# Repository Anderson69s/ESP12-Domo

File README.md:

# ESP12-Domo

More informations : https://atelierdumaker.com/portfolio/esp12-domo/

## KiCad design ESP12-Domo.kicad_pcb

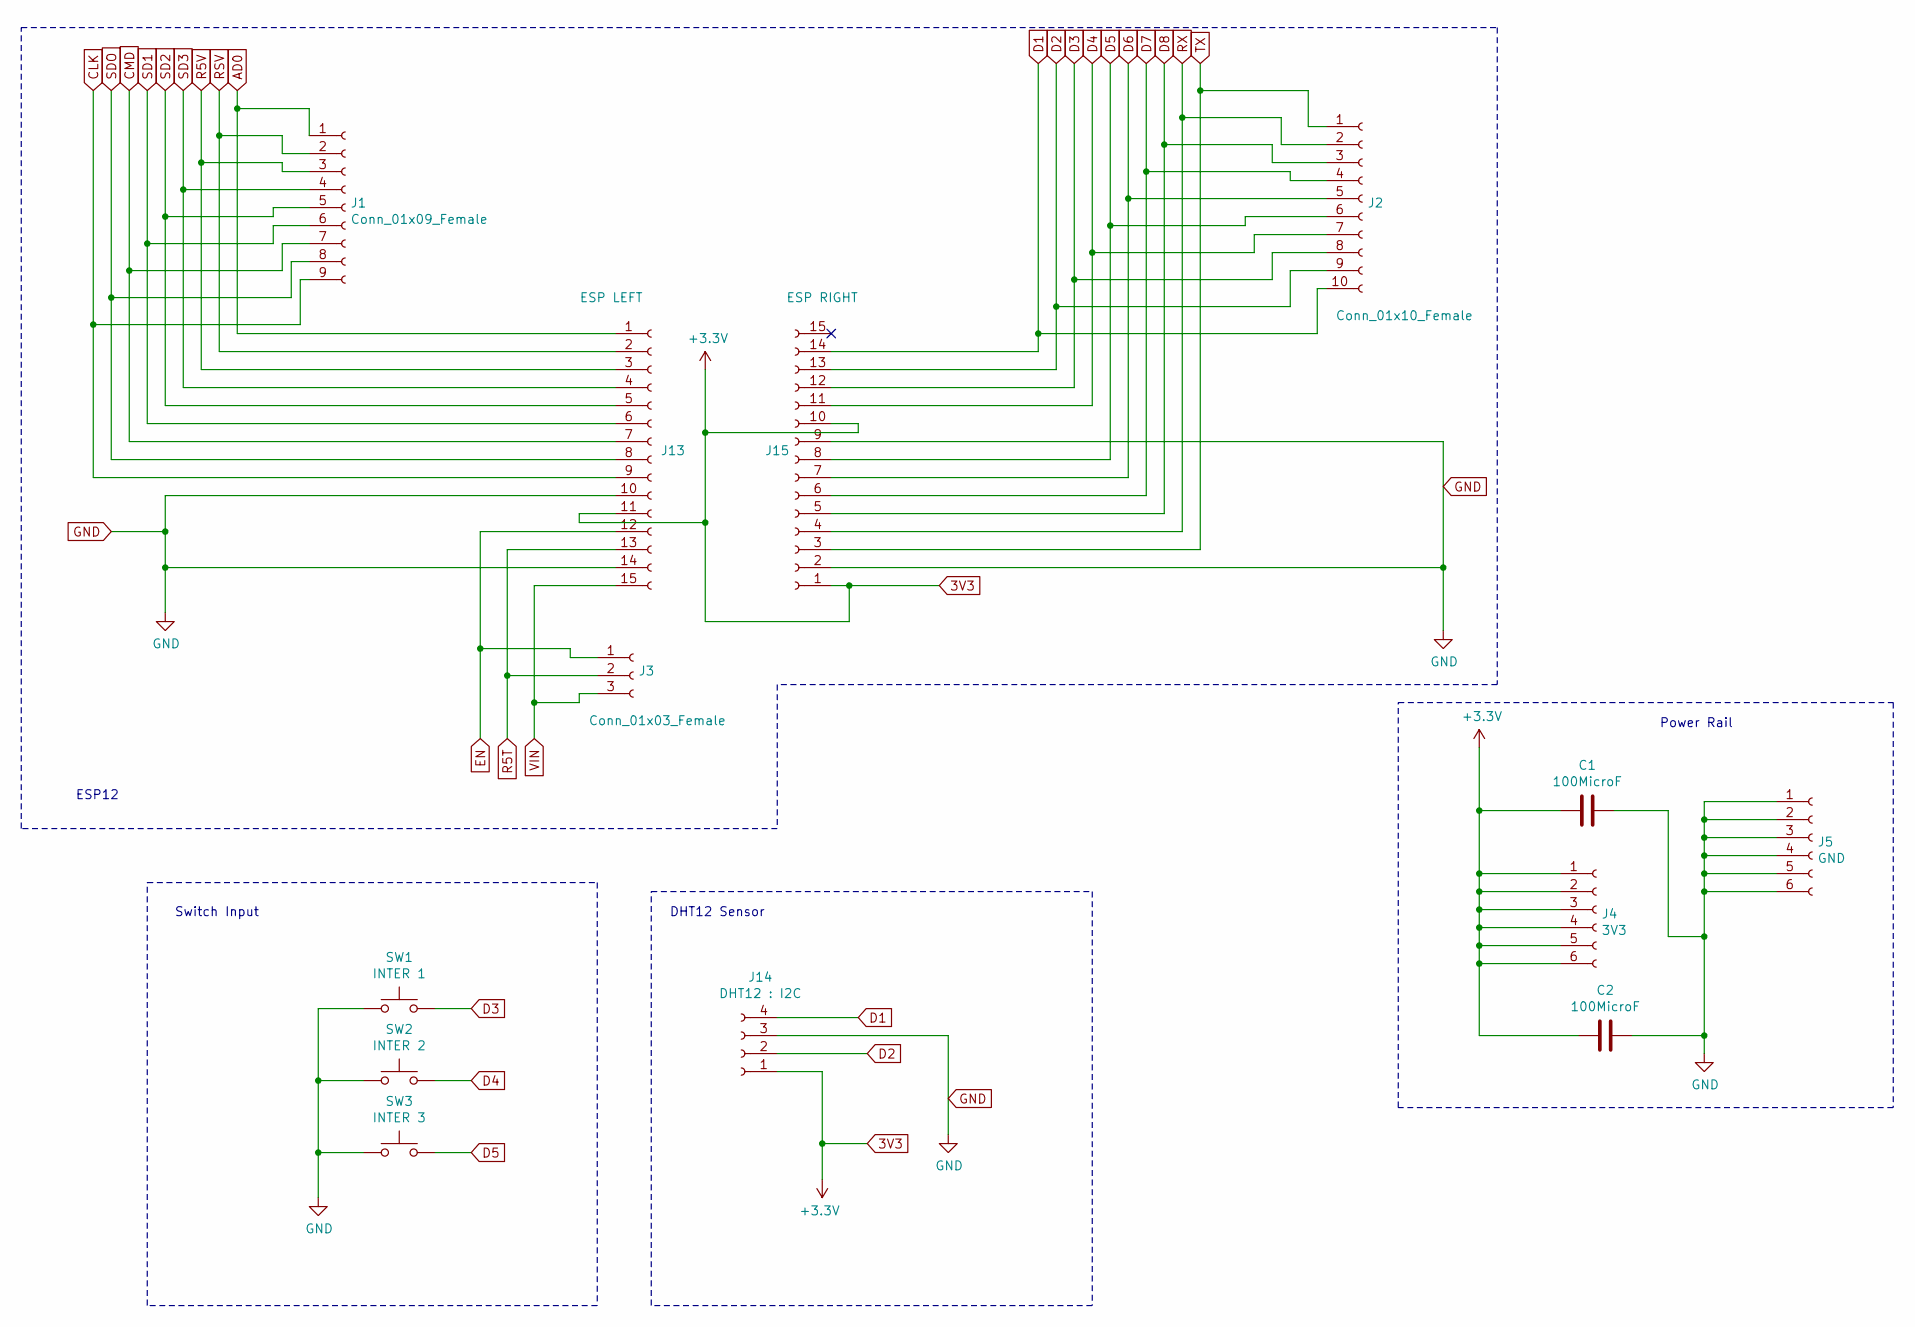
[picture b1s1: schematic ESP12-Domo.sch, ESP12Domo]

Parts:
C1, C2: 100MicroF; SM0805
J1: Conn_01x09_Female; PinHeader_1x09_P2.54mm_Vertical
J2: Conn_01x10_Female; PinHeader_1x10_P2.54mm_Vertical
J3: Conn_01x03_Female; PinHeader_1x03_P2.54mm_Vertical
J4: 3V3; PinHeader_2x03_P2.54mm_Vertical
J5: GND; PinHeader_2x03_P2.54mm_Vertical
J13: ESP LEFT; PinHeader_1x15_P2.54mm_Vertical
J14: DHT12 : I2C; PinHeader_1x04_P2.54mm_Vertical
J15: ESP RIGHT; PinHeader_1x15_P2.54mm_Vertical
SW1: INTER 1; SWITCH_CMS
SW2: INTER 2; SWITCH_CMS
SW3: INTER 3; SWITCH_CMS

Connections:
3V3: C1.2, C2.2, J4.1, J4.2, J4.3, J4.4, J4.5, J4.6, J13.11, J14.1, J15.1, J15.10
AD0: J1.1, J13.1
CLK: J1.9, J13.9
CMD: J1.7, J13.7
D1: J2.10, J14.4, J15.14
D2: J2.9, J14.2, J15.13
D3: J2.8, J15.12, SW1.2
D4: J2.7, J15.11, SW2.2
D5: J2.6, J15.8, SW3.2
D6: J2.5, J15.7
D7: J2.4, J15.6
D8: J2.3, J15.5
EN: J3.1, J13.12
GND: C1.1, C2.1, J5.1, J5.2, J5.3, J5.4, J5.5, J5.6, J13.10, J13.14, J14.3, J15.2, J15.9, SW1.1, SW2.1, SW3.1
R5T: J3.2, J13.13
R5V: J1.3, J13.3
RSV: J1.2, J13.2
RX: J2.2, J15.4
SD1: J1.6, J13.6
SD2: J1.5, J13.5
SD3: J1.4, J13.4
SDO: J1.8, J13.8
TX: J2.1, J15.3
VIN: J3.3, J13.15

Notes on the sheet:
DHT12 Sensor
Switch Input
Power Rail
ESP12

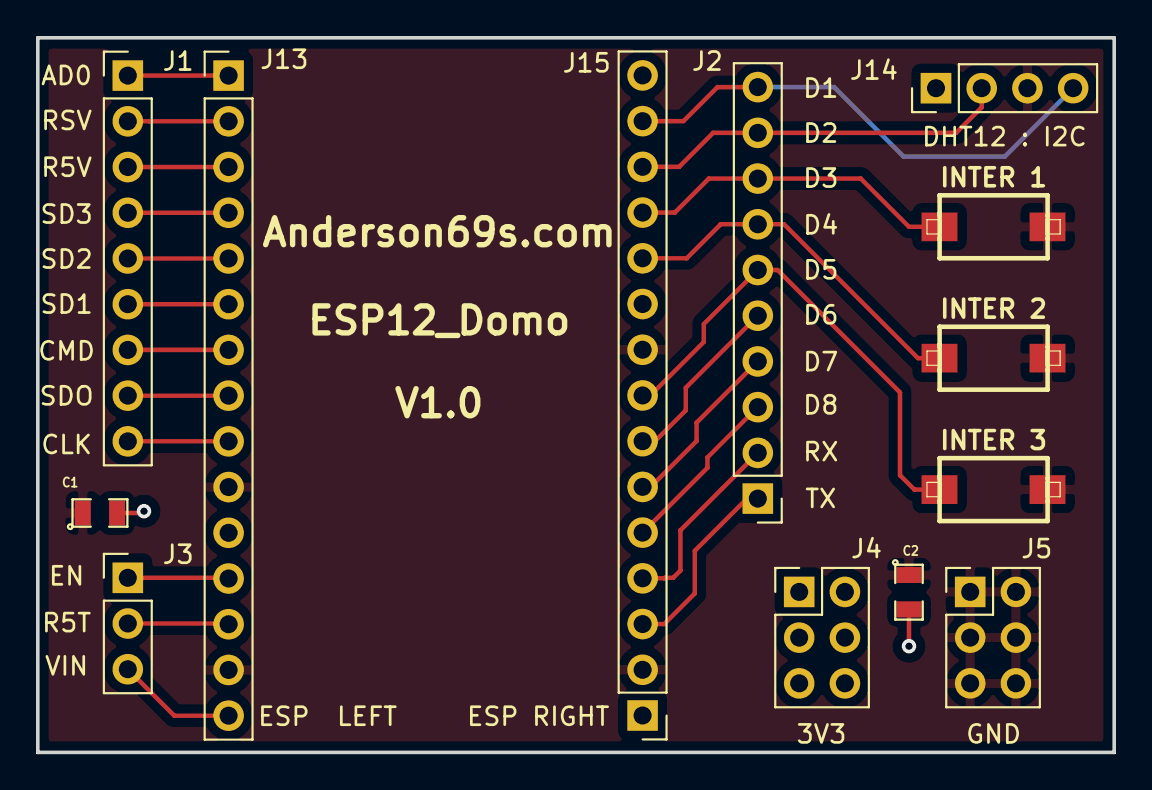
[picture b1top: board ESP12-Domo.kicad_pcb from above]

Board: 2 copper layers, 59.8 x 39.7 mm, 13 parts (0 on the bottom side), 24 nets.

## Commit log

2019-03-17 Clean-Up
2020-04-27 Gerber
    add gerber for easy production
